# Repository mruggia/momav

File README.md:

# MOMAV

Codebase of the MOMAV omnidirectional drone. Further information can be found on the project website: 

[https://marcoruggia.ch/home?projects_momav](https://marcoruggia.ch/home?projects_momav)

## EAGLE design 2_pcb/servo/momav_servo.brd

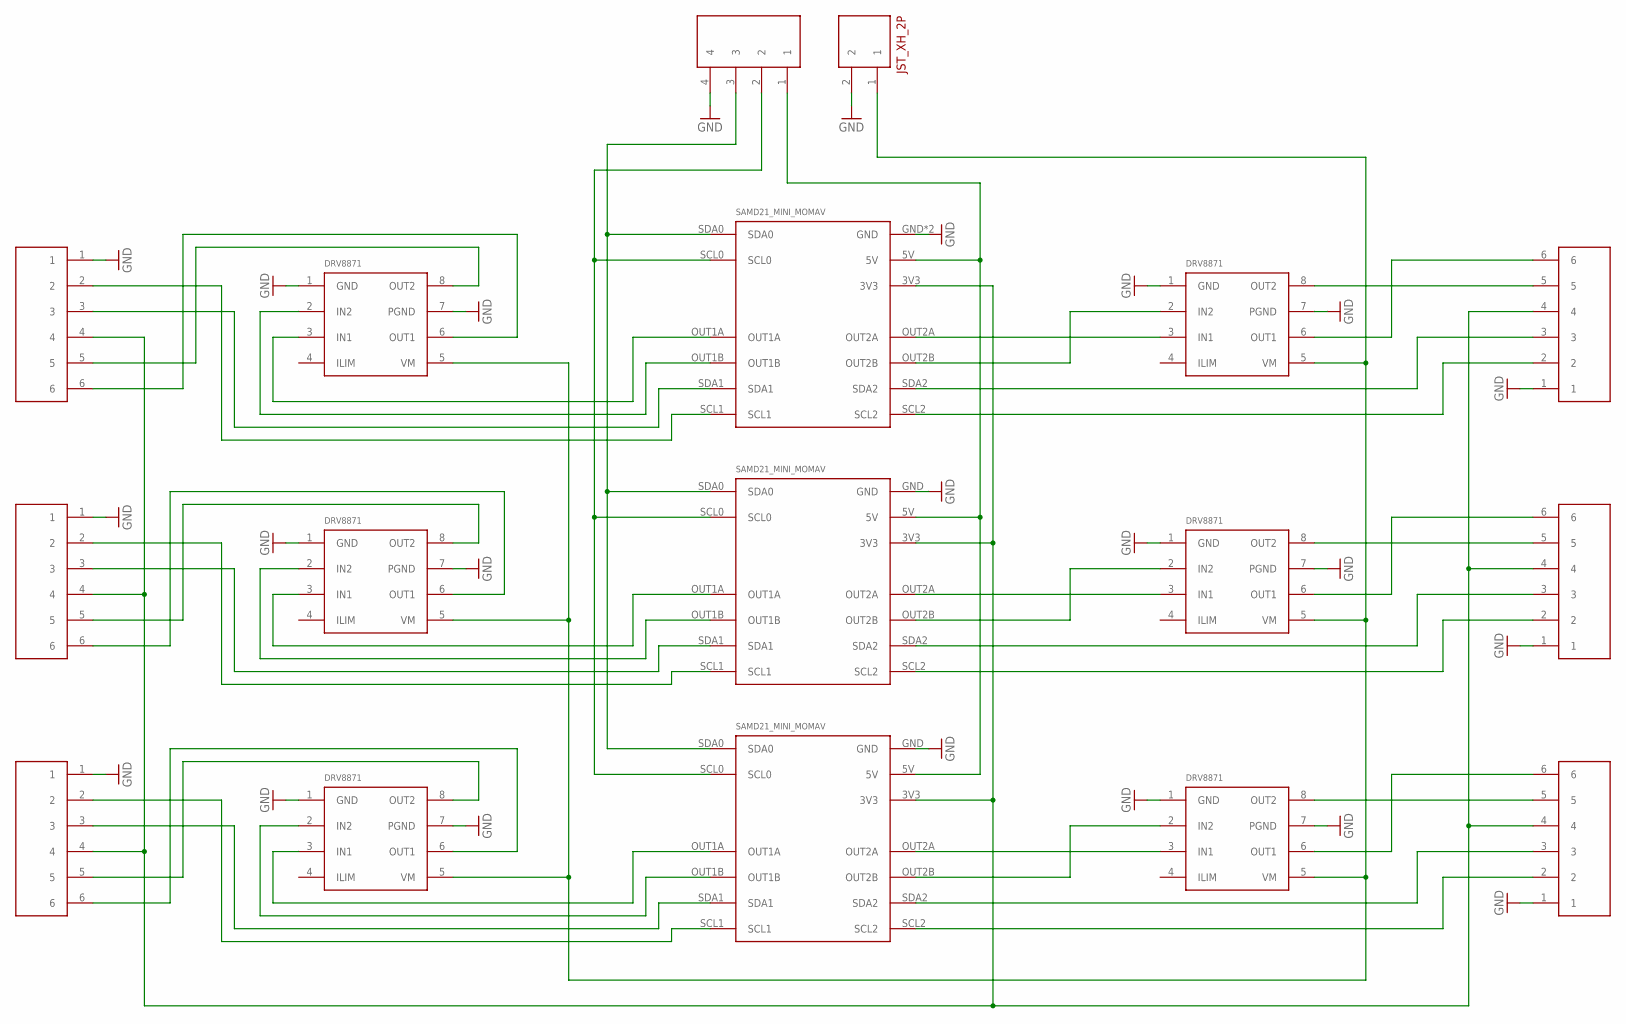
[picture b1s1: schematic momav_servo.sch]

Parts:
U$1, U$2, U$3, U$4, U$5, U$6: DRV8871BOB
U$7: SAMD21_MINI_MOMAV1
U$8, U$9: SAMD21_MINI_MOMAV
U$10: JST_XH_2P
U$11: JST_ZH_4P
U$12, U$13, U$14, U$15, U$16, U$17: JST_ZH_6P

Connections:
GND: U$1.1 (GND), U$1.7 (PGND), U$2.1 (GND), U$2.7 (PGND), U$3.1 (GND), U$3.7 (PGND), U$4.1 (GND), U$4.7 (PGND), U$5.1 (GND), U$5.7 (PGND), U$6.1 (GND), U$6.7 (PGND), U$7.GND, U$7.GND2 (GND), U$8.GND, U$9.GND, U$10.2, U$11.4, U$12.1, U$13.1, U$14.1, U$15.1, U$16.1, U$17.1
unnamed: U$7.SCL1, U$12.2
unnamed: U$1.3 (IN1), U$7.OUT1A
unnamed: U$1.2 (IN2), U$7.OUT1B
unnamed: U$2.3 (IN1), U$8.OUT1A
unnamed: U$2.2 (IN2), U$8.OUT1B
unnamed: U$3.3 (IN1), U$9.OUT1A
unnamed: U$3.2 (IN2), U$9.OUT1B
unnamed: U$4.3 (IN1), U$7.OUT2A
unnamed: U$7.5V, U$8.5V, U$9.5V, U$11.1
unnamed: U$5.3 (IN1), U$8.OUT2A
unnamed: U$5.2 (IN2), U$8.OUT2B
unnamed: U$6.3 (IN1), U$9.OUT2A
unnamed: U$6.2 (IN2), U$9.OUT2B
unnamed: U$7.SDA0, U$8.SDA0, U$9.SDA0, U$11.3
unnamed: U$7.SCL0, U$8.SCL0, U$9.SCL0, U$11.2
unnamed: U$4.2 (IN2), U$7.OUT2B
unnamed: U$9.SCL2, U$15.2
unnamed: U$1.5 (VM), U$2.5 (VM), U$3.5 (VM), U$4.5 (VM), U$5.5 (VM), U$6.5 (VM), U$10.1
unnamed: U$7.SDA1, U$12.3
unnamed: U$8.SDA1, U$13.3
unnamed: U$8.SCL1, U$13.2
unnamed: U$9.SDA1, U$14.3
unnamed: U$9.SCL1, U$14.2
unnamed: U$7.3V3, U$8.3V3, U$9.3V3, U$12.4, U$13.4, U$14.4, U$15.4, U$16.4, U$17.4
unnamed: U$9.SDA2, U$15.3
unnamed: U$8.SCL2, U$16.2
unnamed: U$8.SDA2, U$16.3
unnamed: U$7.SCL2, U$17.2
unnamed: U$7.SDA2, U$17.3
unnamed: U$4.6 (OUT1), U$17.6
unnamed: U$4.8 (OUT2), U$17.5
unnamed: U$5.8 (OUT2), U$16.5
unnamed: U$6.6 (OUT1), U$15.6
unnamed: U$6.8 (OUT2), U$15.5
unnamed: U$1.8 (OUT2), U$12.5
unnamed: U$1.6 (OUT1), U$12.6
unnamed: U$2.8 (OUT2), U$13.5
unnamed: U$2.6 (OUT1), U$13.6
unnamed: U$5.6 (OUT1), U$16.6
unnamed: U$3.6 (OUT1), U$14.6
unnamed: U$3.8 (OUT2), U$14.5

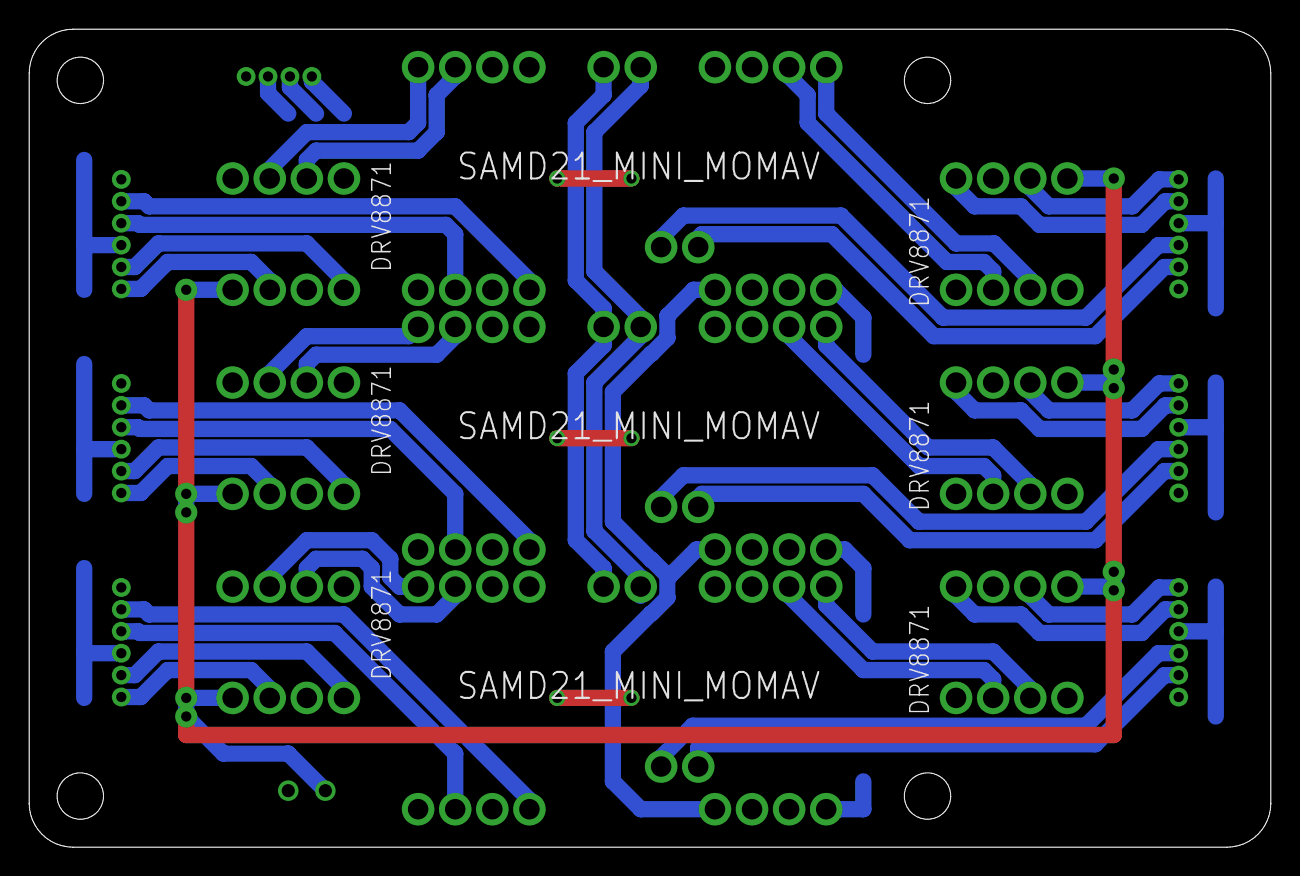
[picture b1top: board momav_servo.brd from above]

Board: 2 copper layers, 85.0 x 56.0 mm, 17 parts (0 on the bottom side), 42 nets.

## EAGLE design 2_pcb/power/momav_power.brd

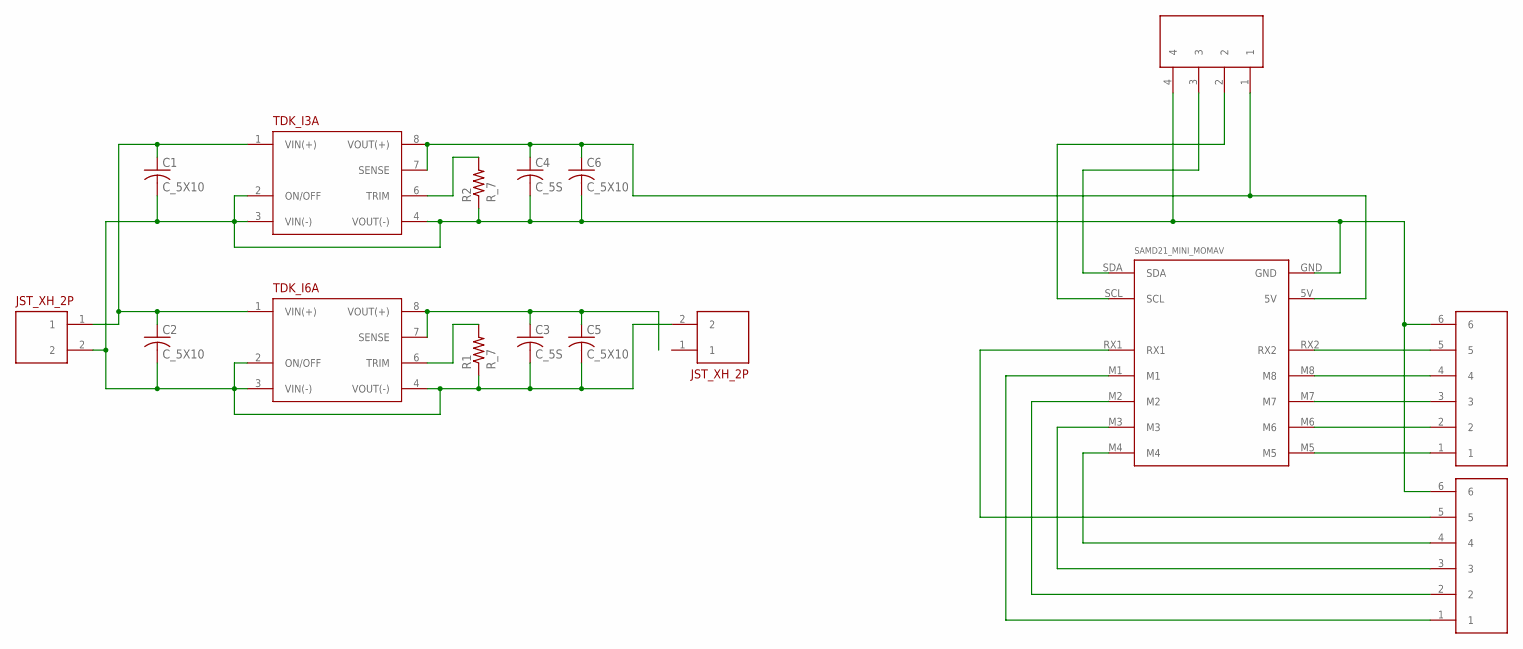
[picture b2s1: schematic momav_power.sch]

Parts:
C1, C2, C5, C6: C_5X10
C3, C4: C_5S
R1, R2: R_7
U$1, U$5: JST_XH_2P
U$2: TDK_I3A
U$3: TDK_I6A
U$4, U$6: JST_ZH_6P
U$7: JST_ZH_4P
U$8: SAMD21_MINI_MOMAV2

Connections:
GND: C1.2, C2.2, C3.2, C4.2, C5.2, C6.2, R1.1, R2.1, U$1.2, U$2.2 (ON/OFF), U$2.3 (VIN(-)), U$2.4 (VOUT(-)), U$3.2 (ON/OFF), U$3.3 (VIN(-)), U$3.4 (VOUT(-)), U$4.6, U$5.2, U$6.6, U$7.4, U$8.GND
unnamed: C4.1, C6.1, U$2.7 (SENSE), U$2.8 (VOUT(+)), U$7.1, U$8.5V
unnamed: C3.1, C5.1, U$3.7 (SENSE), U$3.8 (VOUT(+))
unnamed: C1.1, C2.1, U$2.1 (VIN(+)), U$3.1 (VIN(+)), U$5.1
unnamed: U$7.3, U$8.SDA
unnamed: U$7.2, U$8.SCL
unnamed: U$4.4, U$8.M4
unnamed: R2.2, U$2.6 (TRIM)
unnamed: R1.2, U$3.6 (TRIM)
unnamed: U$4.3, U$8.M3
unnamed: U$4.2, U$8.M2
unnamed: U$4.1, U$8.M1
unnamed: U$6.1, U$8.M5
unnamed: U$6.2, U$8.M6
unnamed: U$6.3, U$8.M7
unnamed: U$6.4, U$8.M8
unnamed: U$6.5, U$8.RX2
unnamed: U$4.5, U$8.RX1

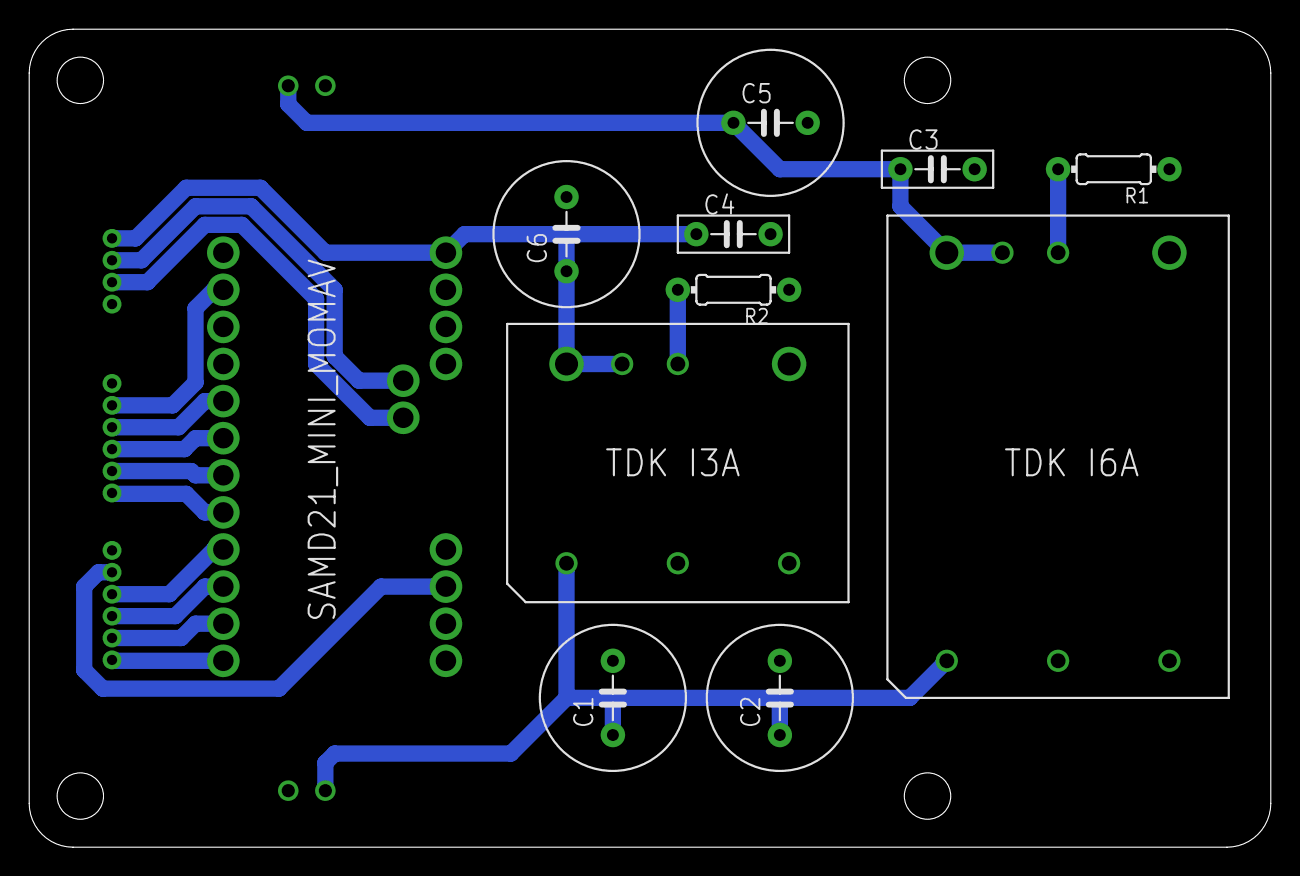
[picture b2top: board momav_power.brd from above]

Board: 2 copper layers, 85.0 x 56.0 mm, 16 parts (0 on the bottom side), 18 nets.

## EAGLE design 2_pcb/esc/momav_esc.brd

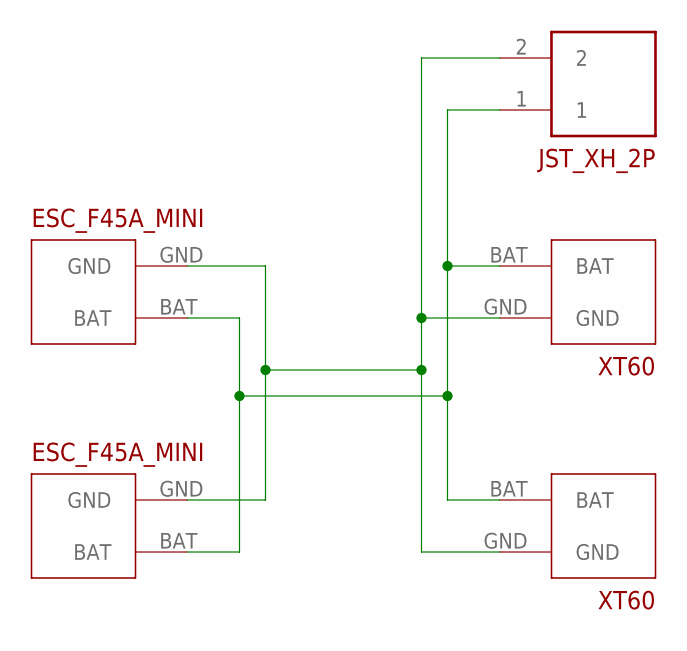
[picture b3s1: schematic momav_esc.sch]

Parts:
U$1, U$2: ESC_F45A_MINI
U$3, U$4: CONN_XT60
U$5: JST_XH_2P

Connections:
unnamed: U$1.GND, U$2.GND, U$3.GND, U$4.GND, U$5.2
unnamed: U$1.BAT, U$2.BAT, U$3.BAT, U$4.BAT, U$5.1

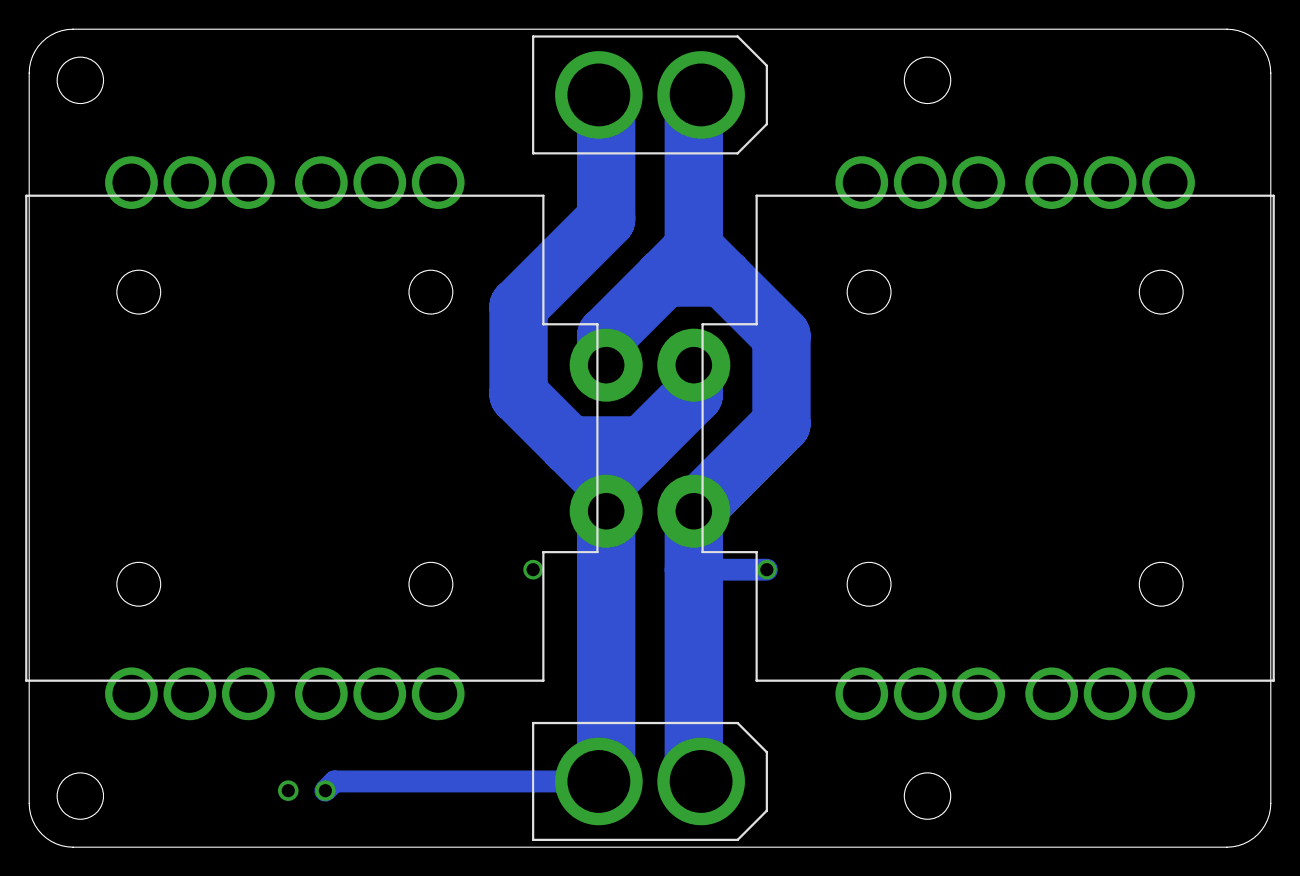
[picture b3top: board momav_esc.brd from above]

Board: 2 copper layers, 85.0 x 56.0 mm, 5 parts (0 on the bottom side), 2 nets.

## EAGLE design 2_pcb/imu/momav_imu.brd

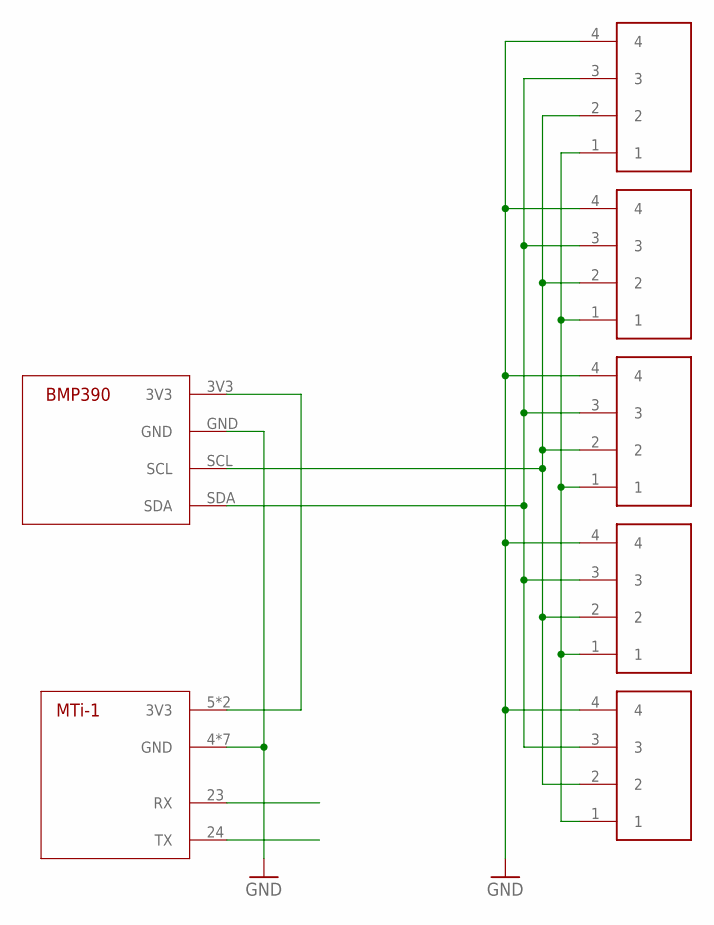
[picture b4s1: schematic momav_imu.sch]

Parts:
U$1, U$2, U$3, U$4, U$5: JST_ZH_4P
U$6: XSENS_MTI_1
U$7: BMP390

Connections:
3V3: U$6.5 (3V3), U$6.7 (3V3), U$7.3V3
5V: U$1.1, U$2.1, U$3.1, U$4.1, U$5.1
GND: U$1.4, U$2.4, U$3.4, U$4.4, U$5.4, U$6.4 (GND), U$6.8 (GND), U$6.13 (GND), U$6.14 (GND), U$6.15 (GND), U$6.22 (GND), U$6.25 (GND), U$7.GND
RX: U$6.23 (RX)
SCL: U$1.2, U$2.2, U$3.2, U$4.2, U$5.2, U$7.SCL
SDA: U$1.3, U$2.3, U$3.3, U$4.3, U$5.3, U$7.SDA
TX: U$6.24 (TX)

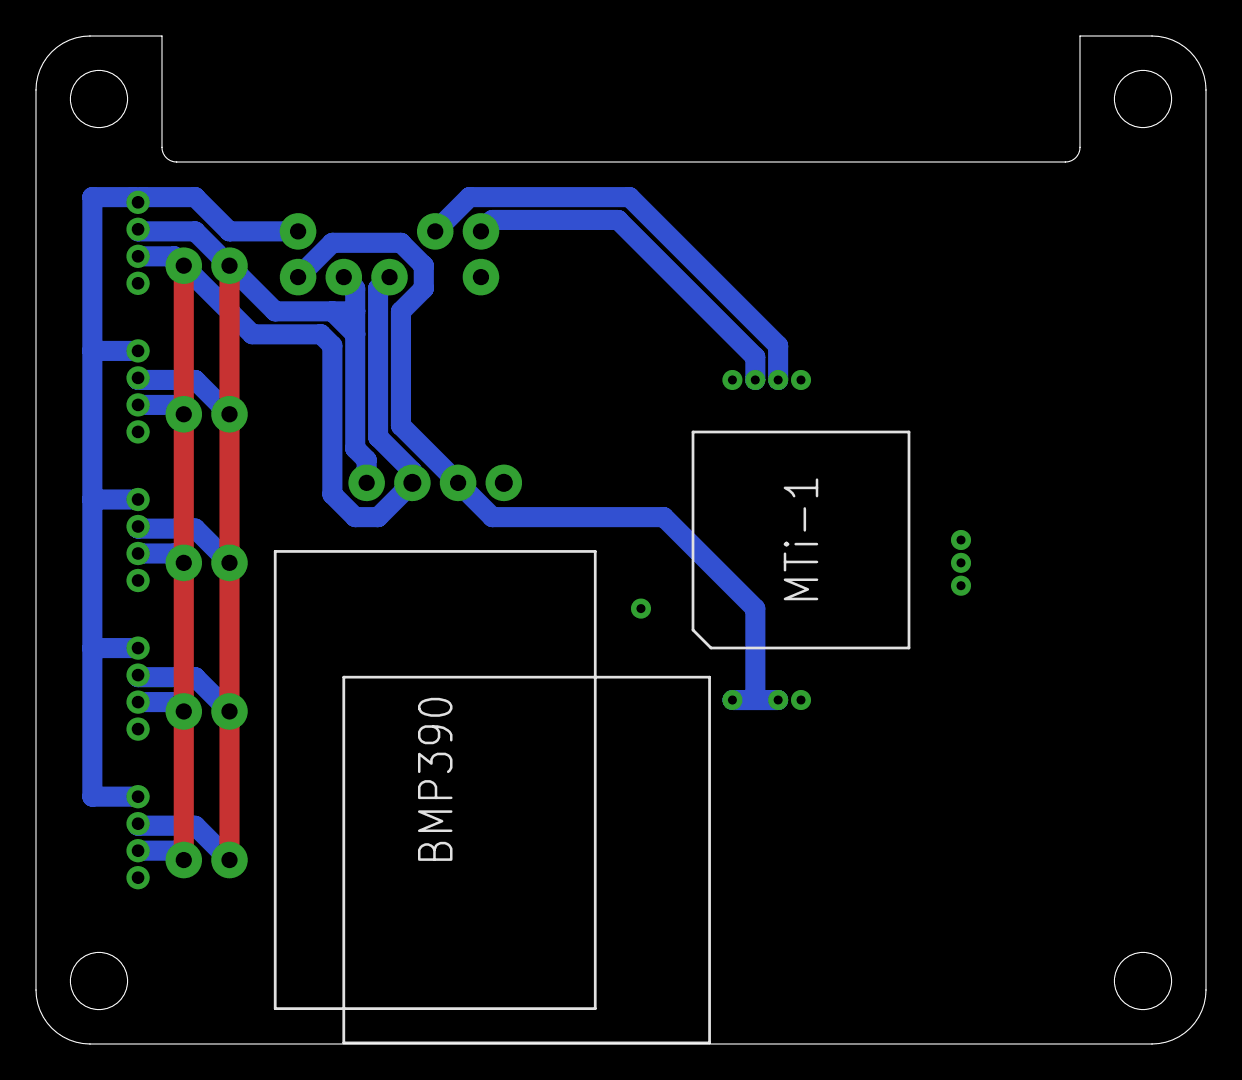
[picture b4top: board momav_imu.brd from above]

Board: 2 copper layers, 65.0 x 56.0 mm, 7 parts (0 on the bottom side), 5 nets.

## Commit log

2024-05-27 main commit
